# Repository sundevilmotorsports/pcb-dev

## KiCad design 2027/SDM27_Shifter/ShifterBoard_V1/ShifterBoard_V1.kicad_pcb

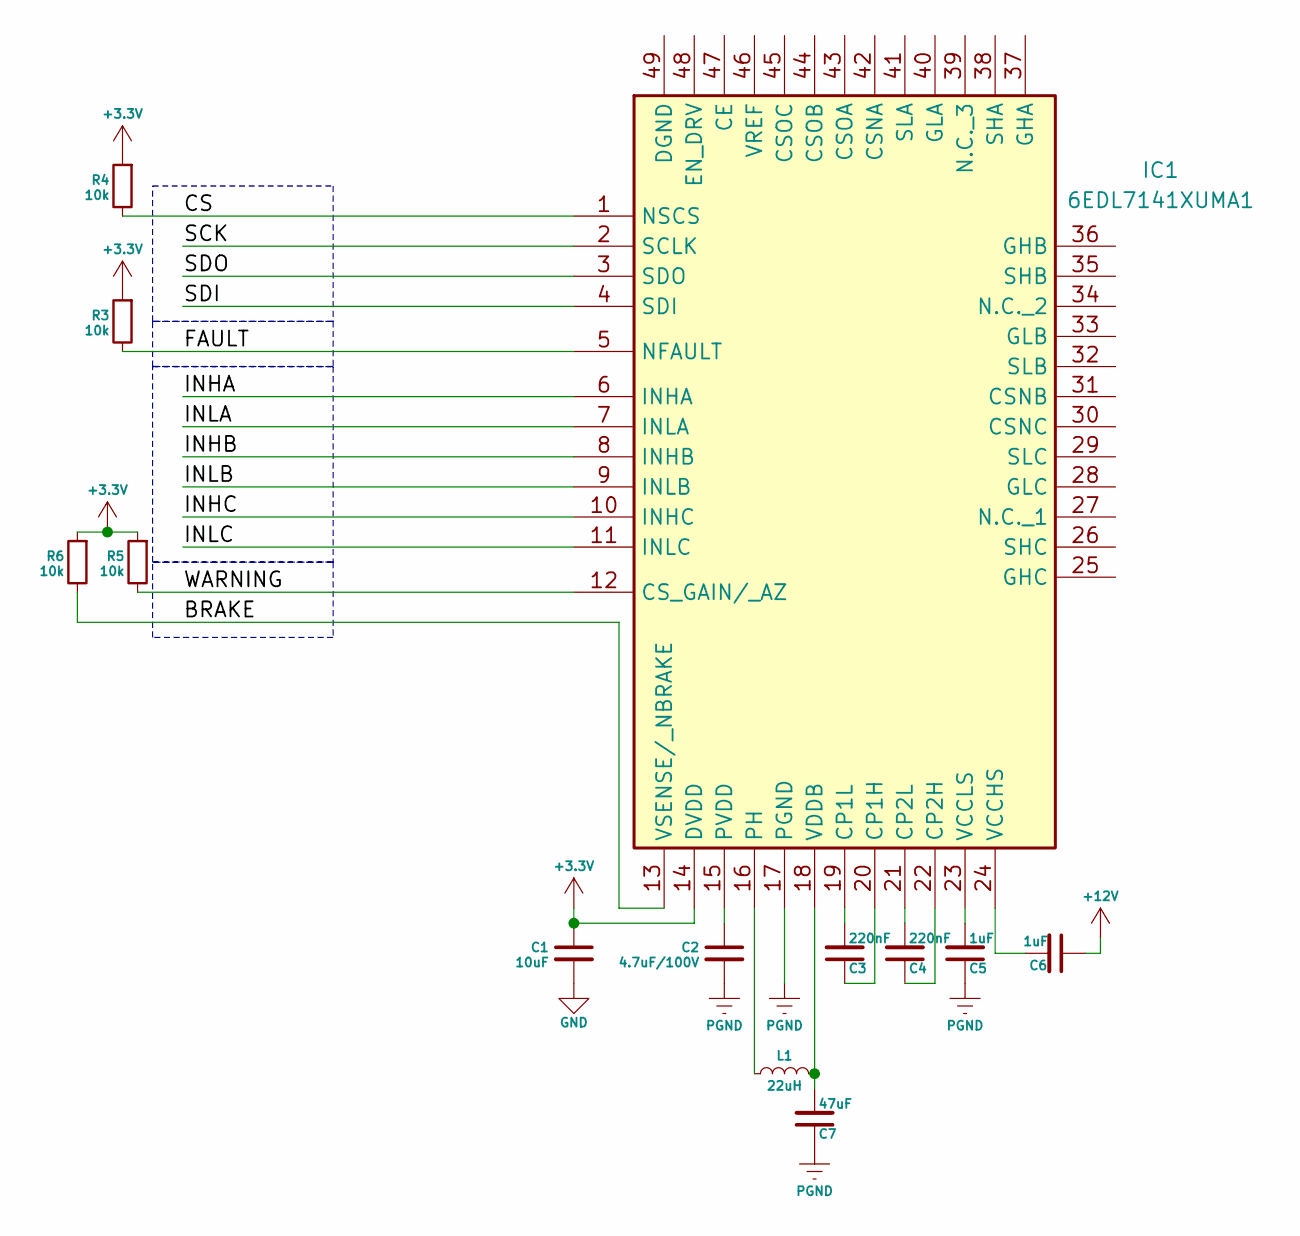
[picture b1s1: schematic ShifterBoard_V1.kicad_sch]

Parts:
C1: 10uF; C_0603_1608Metric
C2: 4.7uF/100V; C_0603_1608Metric
C3, C4: 220nF; C_0603_1608Metric
C5, C6: 1uF; C_0603_1608Metric
C7: 47uF; C_0603_1608Metric
IC1: 6EDL7141XUMA1; Mouser Part Number 726-6EDL7141XUMA1
L1: 22uH; L_1008_2520Metric
R3, R4, R5, R6: 10k; R_0603_1608Metric

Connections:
+3.3V: C1.1, IC1.14 (DVDD), R3.1, R4.1, R5.1, R6.1
+12V: C6.1
/BRAKE: IC1.13 (VSENSE/_NBRAKE), R6.2
/CS: IC1.1 (NSCS), R4.2
/FAULT: IC1.5 (NFAULT), R3.2
/INHA: IC1.6 (INHA)
/INHB: IC1.8 (INHB)
/INHC: IC1.10 (INHC)
/INLA: IC1.7 (INLA)
/INLB: IC1.9 (INLB)
/INLC: IC1.11 (INLC)
/SCK: IC1.2 (SCLK)
/SDI: IC1.4 (SDI)
/SDO: IC1.3 (SDO)
/WARNING: IC1.12 (CS_GAIN/_AZ), R5.2
GND: C1.2
unnamed: C3.1, IC1.20 (CP1H)
unnamed: C3.2, IC1.19 (CP1L)
unnamed: C4.1, IC1.22 (CP2H)
unnamed: C4.2, IC1.21 (CP2L)
unnamed: IC1.16 (PH), L1.1
unnamed: C2.1, IC1.15 (PVDD)
unnamed: C6.2, IC1.24 (VCCHS)
unnamed: C5.2, IC1.23 (VCCLS)
unnamed: C7.2, IC1.18 (VDDB), L1.2
PGND: C2.2, C5.1, C7.1, IC1.17 (PGND)

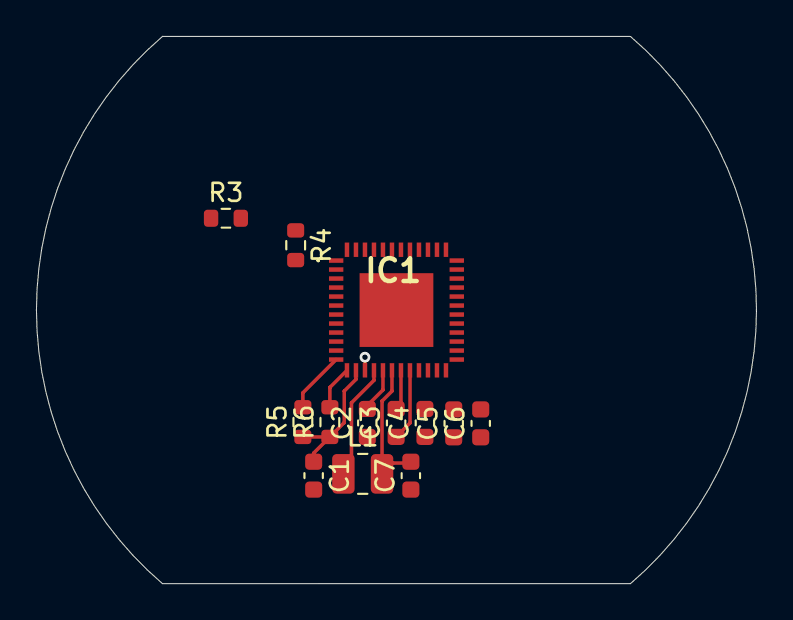
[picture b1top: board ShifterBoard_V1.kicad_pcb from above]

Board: 2 copper layers, 40.0 x 30.4 mm, 13 parts (0 on the bottom side), 15 nets.

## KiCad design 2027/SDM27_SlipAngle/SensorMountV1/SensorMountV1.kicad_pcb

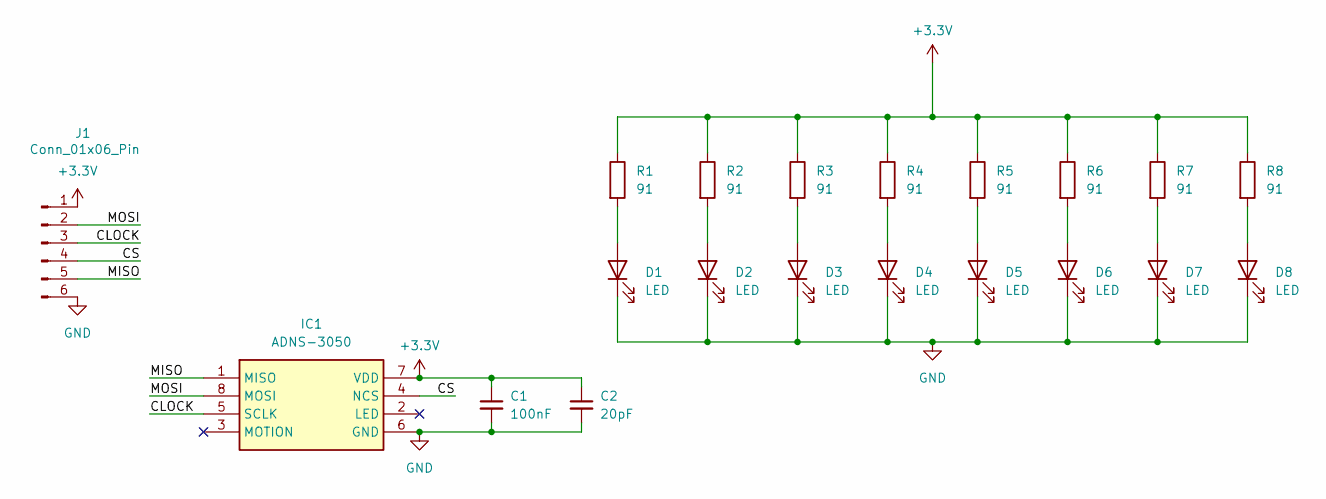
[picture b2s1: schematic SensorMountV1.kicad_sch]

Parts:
C1: 100nF; C_0603_1608Metric
C2: 20pF; C_0603_1608Metric
D1, D2, D3, D4, D5, D6, D7, D8: LED; LED_D5.0mm_Clear
IC1: ADNS-3050; ADNS3050; Mouser Part Number 630-ADNS-3050
J1: Conn_01x06_Pin; JST_XH_B6B-XH-A_1x06_P2.50mm_Vertical
R1, R2, R3, R4, R5, R6, R7, R8: 91; R_Axial_DIN0204_L3.6mm_D1.6mm_P5.08mm_Horizontal

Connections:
+3.3V: C1.1, C2.1, IC1.7 (VDD), J1.1, R1.1, R2.1, R3.1, R4.1, R5.1, R6.1, R7.1, R8.1
/CLOCK: IC1.5 (SCLK), J1.3
/CS: IC1.4 (NCS), J1.4
/MISO: IC1.1 (MISO), J1.5
/MOSI: IC1.8 (MOSI), J1.2
GND: C1.2, C2.2, D1.1 (K), D2.1 (K), D3.1 (K), D4.1 (K), D5.1 (K), D6.1 (K), D7.1 (K), D8.1 (K), IC1.6 (GND), J1.6
unnamed: D1.2 (A), R1.2
unnamed: D2.2 (A), R2.2
unnamed: D3.2 (A), R3.2
unnamed: D4.2 (A), R4.2
unnamed: D5.2 (A), R5.2
unnamed: D6.2 (A), R6.2
unnamed: D7.2 (A), R7.2
unnamed: D8.2 (A), R8.2

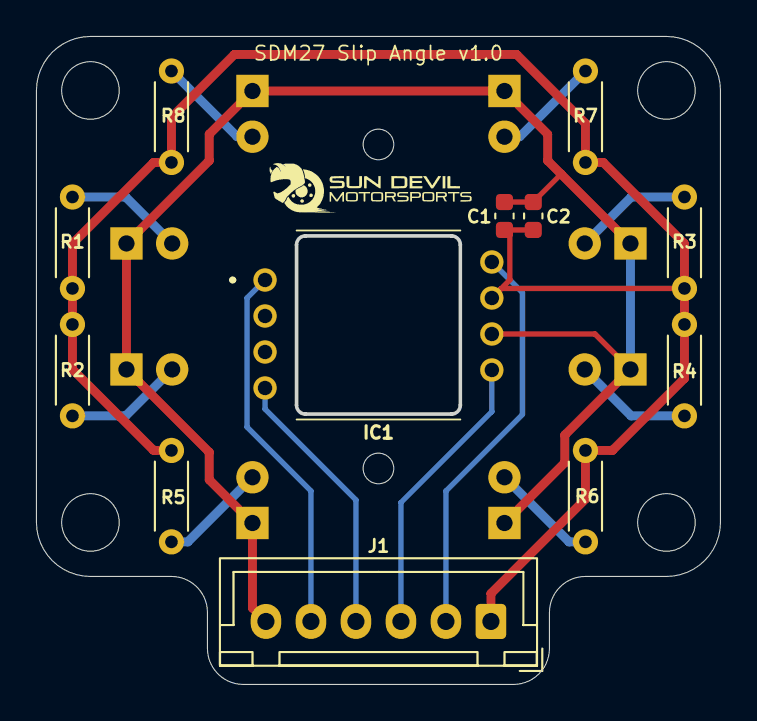
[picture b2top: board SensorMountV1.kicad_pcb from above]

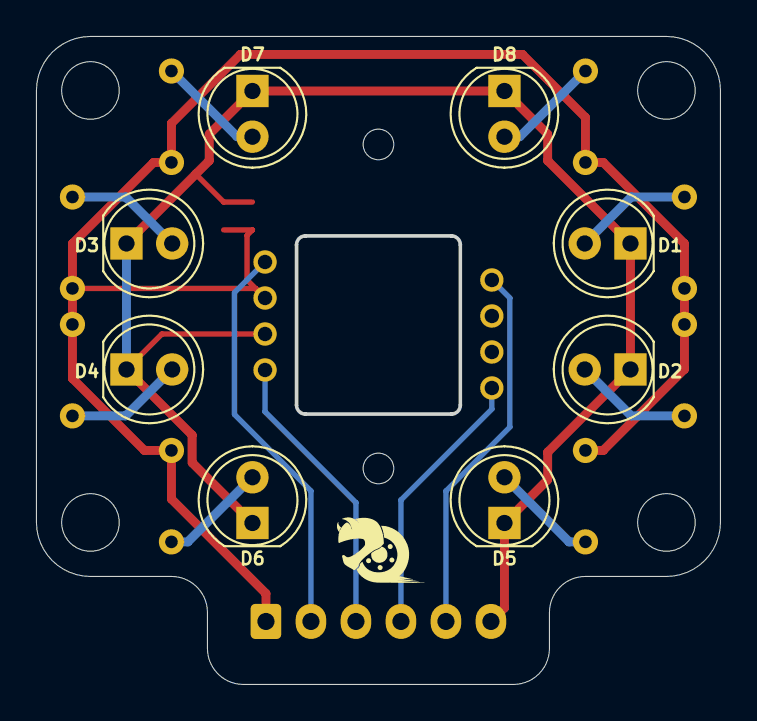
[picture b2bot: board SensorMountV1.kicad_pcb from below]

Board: 2 copper layers, 38.0 x 36.0 mm, 20 parts (8 on the bottom side), 14 nets.

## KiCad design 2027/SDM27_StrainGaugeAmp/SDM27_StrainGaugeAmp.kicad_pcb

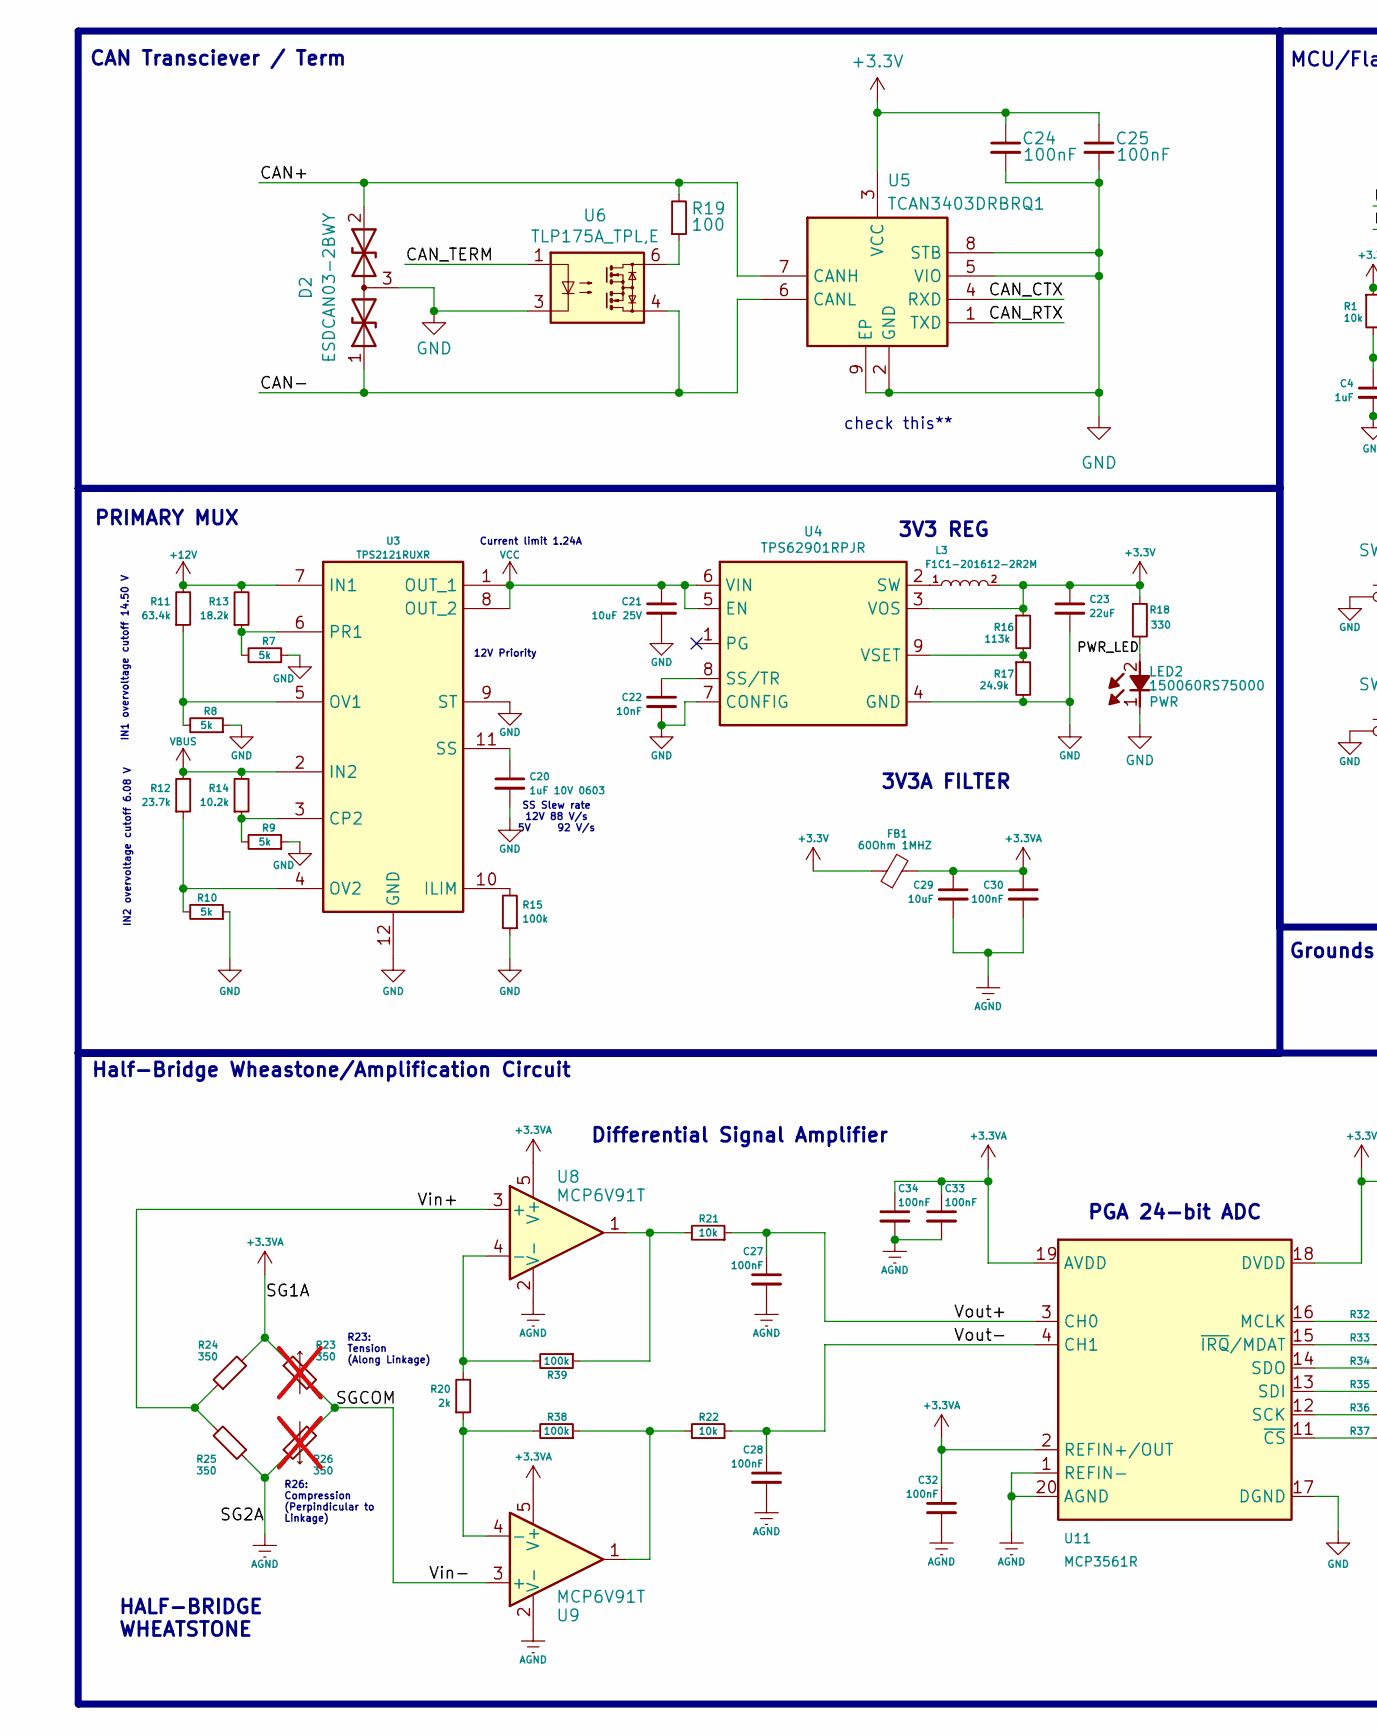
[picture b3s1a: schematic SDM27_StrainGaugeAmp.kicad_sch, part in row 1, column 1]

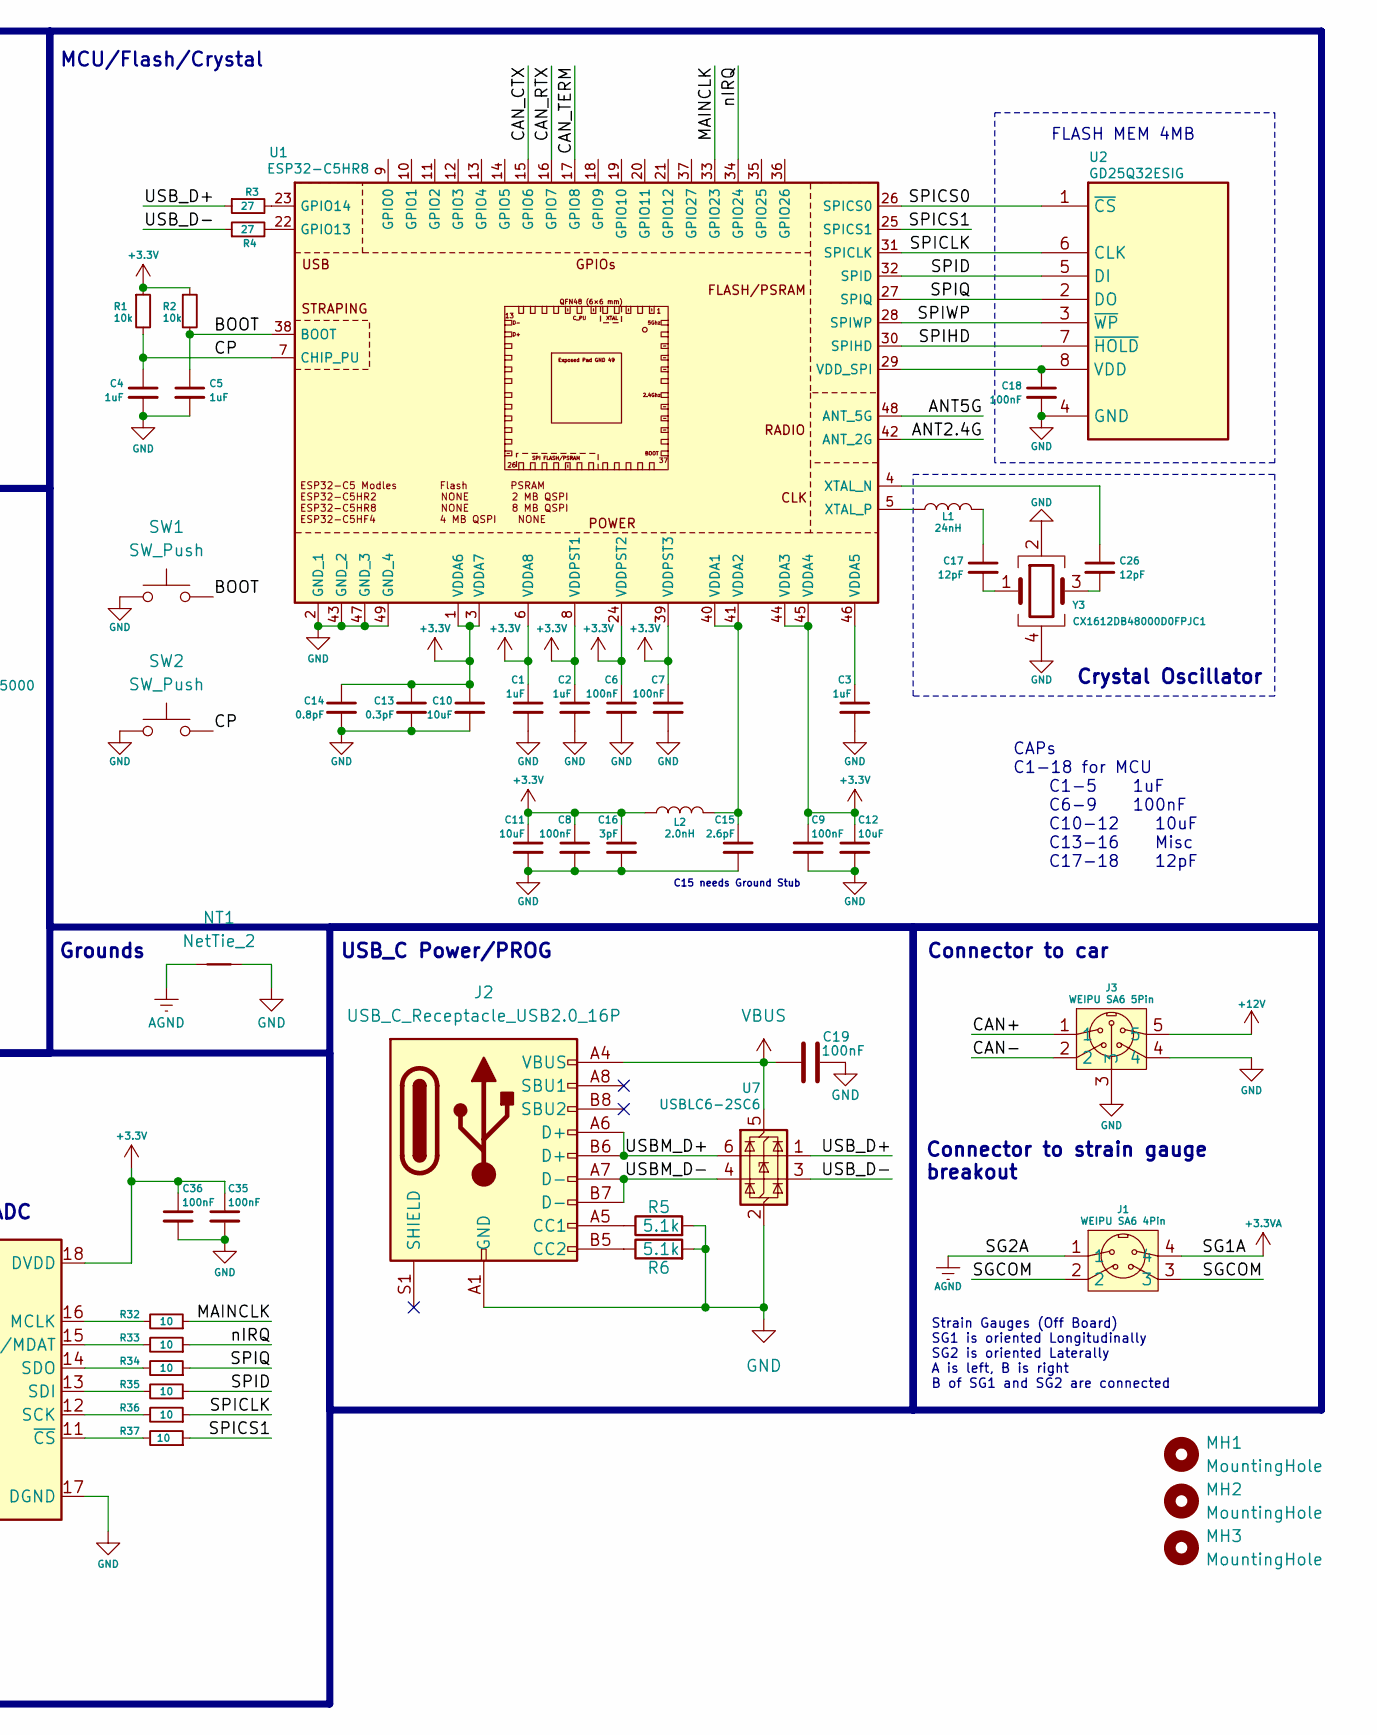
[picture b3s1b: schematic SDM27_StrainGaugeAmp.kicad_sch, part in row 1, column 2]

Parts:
C1, C2, C3, C4, C5: 1uF; C_0603_1608Metric
C6, C7, C8, C9, C18, C19, C24, C25, C27, C28, C30, C32, C33, C34, C35, C36: 100nF; C_0603_1608Metric
C10, C11, C12, C29: 10uF; C_0603_1608Metric
C13: 0.3pF; C_0603_1608Metric
C14: 0.8pF; C_0603_1608Metric
C15: 2.6pF; C_0603_1608Metric
C16: 3pF; C_0603_1608Metric
C17, C26: 12pF; C_0603_1608Metric
C20: 1uF 10V 0603; C_0603_1608Metric
C21: 10uF 25V; C_0603_1608Metric
C22: 10nF; C_0603_1608Metric
C23: 22uF; C_0603_1608Metric
D2: ESDCAN03-2BWY; SOT65P210X110-3N; Mouser Part Number 511-ESDCAN03-2BWY
FB1: 60Ohm 1MHZ; L_0603_1608Metric
J1: WEIPU SA6 4Pin; JST_EH_S4B-EH_1x04_P2.50mm_Horizontal
J2: USB_C_Receptacle_USB2.0_16P; USB_C_Receptacle_G-Switch_GT-USB-7010ASV
J3: WEIPU SA6 5Pin; JST_EH_S5B-EH_1x05_P2.50mm_Horizontal
L1: 24nH; L_0402_1005Metric
L2: 2.0nH; L_0402_1005Metric
L3: F1C1-201612-2R2M; F1C12016122R2M; Mouser Part Number 530-F1C1-201612-2R2M
LED2: 150060RS75000; LEDC1608X80N; Mouser Part Number 710-150060RS75000
MH1, MH2, MH3: MountingHole; MountingHole_2mm
NT1: NetTie_2; NetTie-2_SMD_Pad0.5mm
R1, R2, R21, R22: 10k; R_0603_1608Metric
R3, R4: 27; R_0402_1005Metric
R5, R6: 5.1k; R_0603_1608Metric
R7, R8, R9, R10: 5k; R_0603_1608Metric
R11: 63.4k; R_0603_1608Metric
R12: 23.7k; R_0603_1608Metric
R13: 18.2k; R_0603_1608Metric
R14: 10.2k; R_0603_1608Metric
R15, R38, R39: 100k; R_0603_1608Metric
R16: 113k; R_0603_1608Metric
R17: 24.9k; R_0603_1608Metric
R18: 330; R_0603_1608Metric
R19: 100; R_0603_1608Metric
R20: 2k; R_0603_1608Metric
R23, R26: 350; R_0603_1608Metric; not fitted
R24, R25: 350; R_0603_1608Metric
R32, R33, R34, R35, R36, R37: 10; R_0603_1608Metric
SW1, SW2: SW_Push; SW_SPST_CK_KXT3
U1: ESP32-C5HR8; QFN40P600X600X90-49N-D; Manufacturer_Part_Number ESP32-C5HR8
U2: GD25Q32ESIG; SOP-8-1EP_4.57x4.57mm_P1.27mm_EP4.57x4.45mm; Mouser Part Number 363-GD25Q32ESIG
U3: TPS2121RUXR; Mouser Part Number 595-TPS2121RUXR
U4: TPS62901RPJR; Mouser Part Number 595-TPS62901RPJR
U5: TCAN3403DRBRQ1; SON65P300X300X100-9N-D; Manufacturer_Part_Number TCAN3403DRBRQ1; Mouser Part Number 595-TCAN3403DRBRQ1
U6: TLP175A_TPL,E; TLP266J; Mouser Part Number 757-TLP175A(TPLE
U7: USBLC6-2SC6; SOT-23-6
U8, U9: MCP6V91T; SOT-23-5
U11: MCP3561R; UQFN-20_3x3mm_P0.55mm
Y3: CX1612DB48000D0FPJC1; Mouser Part Number 581-CX1612DB48D0FPJ

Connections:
+3.3V: C1.1, C2.1, C6.1, C7.1, C8.1, C9.1, C10.1, C11.1, C12.1, C13.1, C14.1, C16.1, C23.1, C24.1, C25.1, C35.1, C36.1, FB1.1, L2.2, L3.2, R1.1, R2.1, R16.1, R18.1, U1.1 (VDDA6), U1.3 (VDDA7), U1.6 (VDDA8), U1.8 (VDDPST1), U1.24 (VDDPST2), U1.39 (VDDPST3), U1.44 (VDDA3), U1.45 (VDDA4), U4.3 (VOS), U5.3 (VCC), U11.18 (DVDD)
+3.3VA: C29.1, C30.1, C32.1, C33.1, C34.1, FB1.2, J1.4, R23.1, R24.2, U8.5 (V+), U9.5 (V+), U11.2 (REFIN+/OUT), U11.19 (AVDD)
+12V: J3.5, R11.2, R13.2, U3.7 (IN1)
/ANT2.4G: U1.42 (ANT_2G)
/ANT5G: U1.48 (ANT_5G)
/BOOT: C5.1, R2.2, SW1.2, U1.38 (BOOT)
/CAN+: D2.2, J3.1, R19.2, U5.7 (CANH)
/CAN-: D2.1, J3.2, U5.6 (CANL), U6.4
/CAN_CTX: U1.15 (GPIO6), U5.4 (RXD)
/CAN_RTX: U1.16 (GPIO7), U5.1 (TXD)
/CAN_TERM: U1.17 (GPIO8), U6.1
/CP: C4.1, R1.2, SW2.2, U1.7 (CHIP_PU)
/MAINCLK: R32.1, U1.33 (GPIO23)
/PWR_LED: LED2.2 (A), R18.2
/SGCOM: J1.2, J1.3, R23.2, R26.2, U9.3 (+)
/SPICLK: R36.1, U1.31 (SPICLK), U2.6 (CLK)
/SPICS0: U1.26 (SPICS0), U2.1 (~CS)
/SPICS1: R37.1, U1.25 (SPICS1)
/SPID: R35.1, U1.32 (SPID), U2.5 (DI)
/SPIHD: U1.30 (SPIHD), U2.7 (~HOLD)
/SPIQ: R34.1, U1.27 (SPIQ), U2.2 (DO)
/SPIWP: U1.28 (SPIWP), U2.3 (~WP)
/USBM_D+: J2.A6 (D+), J2.B6 (D+), U7.6 (I/O1)
/USBM_D-: J2.A7 (D-), J2.B7 (D-), U7.4 (I/O2)
/USB_D+: R3.1, U7.1 (I/O1)
/USB_D-: R4.1, U7.3 (I/O2)
/Vin+: R24.1, R25.2, U8.3 (+)
/Vout+: C27.1, R21.1, U11.3 (CH0)
/Vout-: C28.1, R22.1, U11.4 (CH1)
/nIRQ: R33.1, U1.34 (GPIO24)
AGND: C27.2, C28.2, C29.2, C30.2, C32.2, C33.2, C34.2, J1.1, NT1.1, R25.1, R26.1, U8.2 (V-), U9.2 (V-), U11.1 (REFIN-), U11.20 (AGND)
GND: C1.2, C2.2, C3.2, C4.2, C5.2, C6.2, C7.2, C8.2, C9.2, C10.2, C11.2, C12.2, C13.2, C14.2, C15.2, C16.2, C18.2, C19.1, C20.2, C21.2, C22.2, C23.2, C24.2, C25.2, C35.2, C36.2, D2.3, J2.A1 (GND), J2.A12 (GND), J2.B1 (GND), J2.B12 (GND), J3.3, J3.4, LED2.1 (K), NT1.2, R5.2, R6.2, R7.1, R8.1, R9.1, R10.1, R15.1, R17.2, SW1.1, SW2.1, U1.2 (GND_1), U1.43 (GND_2), U1.47 (GND_3), U1.49 (GND_4), U2.4 (GND), U3.9 (ST), U3.12 (GND), U4.4 (GND), U4.7 (CONFIG), U5.2 (GND), U5.5 (VIO), U5.8 (STB), U5.9 (EP), U6.3, U7.2 (GND), U11.17 (DGND), Y3.2, Y3.4
unnamed: C17.1, L1.2
unnamed: C17.2, Y3.1
unnamed: C26.2, Y3.3
unnamed: J2.A5 (CC1), R5.1
unnamed: J2.B5 (CC2), R6.1
unnamed: R19.1, U6.6
unnamed: R21.2, R39.1, U8.1
unnamed: R22.2, R38.1, U9.1
unnamed: R4.2, U1.22 (GPIO13)
unnamed: R3.2, U1.23 (GPIO14)
unnamed: C15.1, L2.1, U1.40 (VDDA1), U1.41 (VDDA2)
unnamed: C3.1, U1.46 (VDDA5)
unnamed: C18.1, U1.29 (VDD_SPI), U2.8 (VDD)
unnamed: C26.1, U1.4 (XTAL_N)
unnamed: L1.1, U1.5 (XTAL_P)
unnamed: R9.2, R14.1, U3.3 (CP2)
unnamed: R15.2, U3.10 (ILIM)
unnamed: R8.2, R11.1, U3.5 (OV1)
unnamed: R10.2, R12.1, U3.4 (OV2)
unnamed: R7.2, R13.1, U3.6 (PR1)
unnamed: C20.1, U3.11 (SS)
unnamed: C22.1, U4.8 (SS/TR)
unnamed: L3.1, U4.2 (SW)
unnamed: R16.2, R17.1, U4.9 (VSET)
unnamed: R20.2, R39.2, U8.4 (-)
unnamed: R20.1, R38.2, U9.4 (-)
unnamed: R32.2, U11.16 (MCLK)
unnamed: R36.2, U11.12 (SCK)
unnamed: R35.2, U11.13 (SDI)
unnamed: R34.2, U11.14 (SDO)
unnamed: R37.2, U11.11 (~CS)
unnamed: R33.2, U11.15 (~IRQ/MDAT)
VBUS: C19.2, J2.A4 (VBUS), J2.A9 (VBUS), J2.B4 (VBUS), J2.B9 (VBUS), R12.2, R14.2, U3.2 (IN2), U7.5 (VBUS)
VCC: C21.1, U3.1 (OUT_1), U3.8 (OUT_2), U4.5 (EN), U4.6 (VIN)

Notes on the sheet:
check this**
FLASH MEM 4MB
3V3 REG
R23: Tension (Along Linkage)
SS Slew rate 12V 88 V/s 5V 92 V/s
Current limit 1.24A
Connector to car
Connector to strain gauge breakout
C15 needs Ground Stub
12V Priority
CAN Transciever / Term
IN2 overvoltage cutoff 6.08 V
MCU/Flash/Crystal
Half-Bridge Wheastone/Amplification Circuit
Differential Signal Amplifier
3V3A FILTER
HALF-BRIDGE WHEATSTONE
R26: Compression (Perpindicular to Linkage)
CAPs C1-18 for MCU C1-5 1uF C6-9 100nF C10-12 10uF C13-16 Misc C17-18 12pF
Crystal Oscillator
PGA 24-bit ADC
PRIMARY MUX
Grounds
Strain Gauges (Off Board) SG1 is oriented Longitudinally SG2 is oriented Laterally A is left, B is right B of SG1 and SG2 are connected
USB_C Power/PROG
IN1 overvoltage cutoff 14.50 V

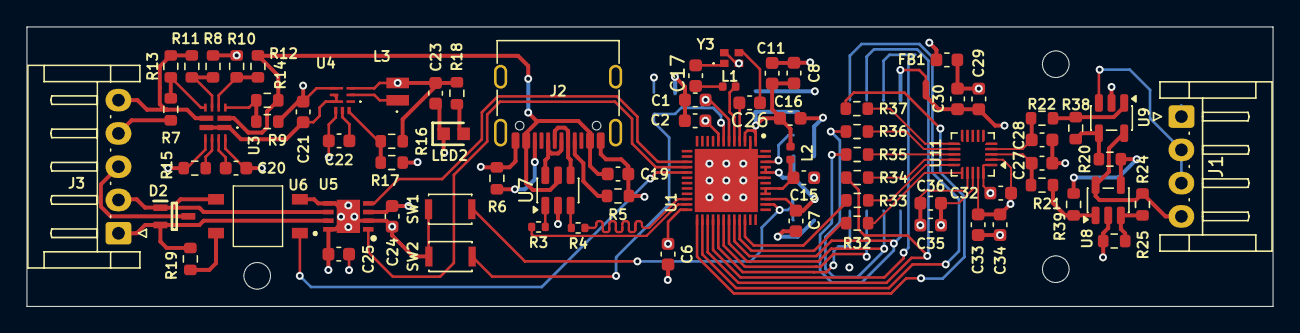
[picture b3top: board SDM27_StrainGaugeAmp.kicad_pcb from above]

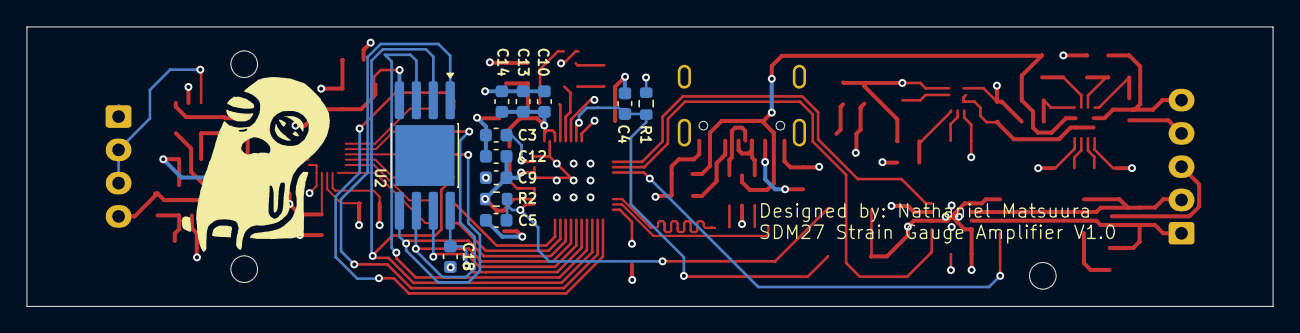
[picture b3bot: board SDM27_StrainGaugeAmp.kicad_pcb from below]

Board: 4 copper layers, 93.6 x 21.0 mm, 91 parts (12 on the bottom side), 64 nets.

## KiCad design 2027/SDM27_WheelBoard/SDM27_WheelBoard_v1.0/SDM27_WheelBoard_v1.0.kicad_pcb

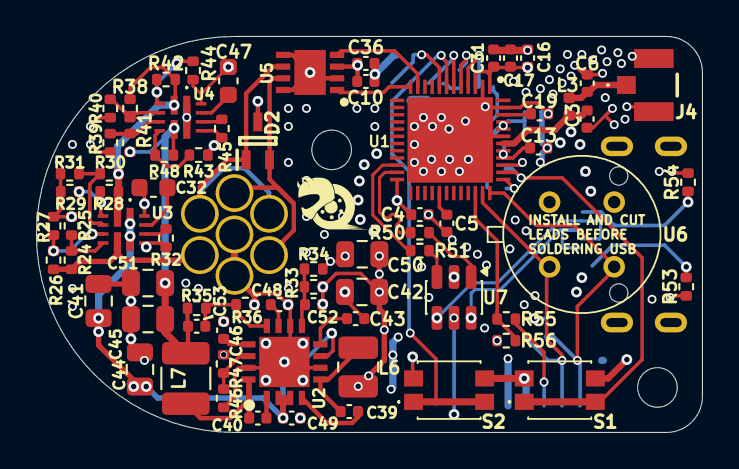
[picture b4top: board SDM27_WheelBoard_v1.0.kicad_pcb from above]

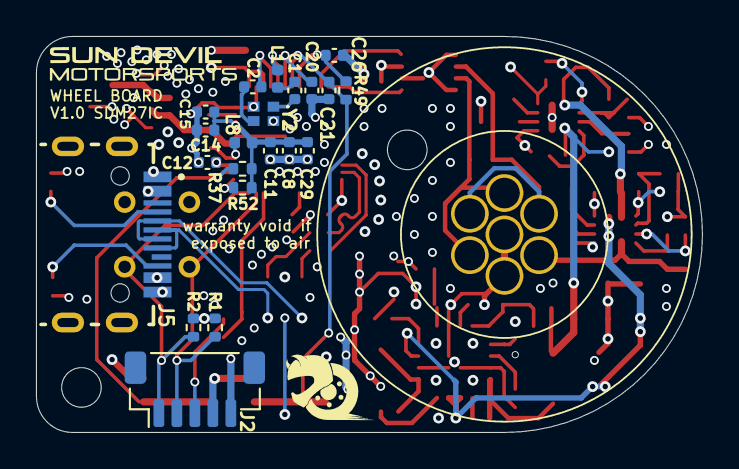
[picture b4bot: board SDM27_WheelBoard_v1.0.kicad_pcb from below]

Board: 4 copper layers, 37.0 x 22.0 mm, 95 parts (22 on the bottom side), 58 nets.

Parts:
C1, C2: 12pF; C_0402_1005Metric
C3, C6: 2.2pF 25V NPO; C_0402_1005Metric
C4, C5, C8, C12, C15: 0.1uF; C_0402_1005Metric
C10, C36, C39, C40, C49: 100nF; C_0402_1005Metric
C11: 3pF; C_0402_1005Metric
C13: 2.6pF; C_0402_1005Metric
C14, C29, C31: 10uF; C_0402_1005Metric
C16: 0.8pF; C_0402_1005Metric
C17: 0.3pF; C_0402_1005Metric
C19, C20, C21, C26, C48: 1uF; C_0402_1005Metric
C32, C47: 1uF 10V 0603; C_0603_1608Metric
C41, C44: 10uF 25V; C_0805_2012Metric
C42, C50: 22uF 10V; C_0805_2012Metric
C43, C46: 10nF; C_0402_1005Metric
C45, C51: 22uF 16V; C_0805_2012Metric
C52, C53: 10pF; C_0402_1005Metric
D2: ESDCAN03-2BWY; SOT65P210X110-3N
H1, H2: M2; MountingHole_2.2mm_M2
J1: WEIPU SA12 7PIN; SA12 7Pin
J2: WEIPU SA6 5Pin; JST_SH_BM05B-SRSS-TB_1x05-1MP_P1.00mm_Vertical
J4: UFL; CONUFL001SMDT
J5: USB4725-03-C-KIT; GCT_USB4730-GF-A_REVA
L1: 24nH; L_0402_1005Metric
L3: 2.8nH; L_0402_1005Metric
L6: 2.2uH; L_1008_2520Metric
L7: 4.7uH; L_1210_3225Metric
L8: 2.0nH; L_0402_1005Metric
R1, R2, R37, R47, R49, R52, R55: 10k; R_0402_1005Metric
R24: 18.2k; R_0402_1005Metric
R25, R27, R29, R31, R39, R40, R43, R44: 5k; R_0402_1005Metric
R26: 63.4k; R_0402_1005Metric
R28, R42: 10.2k; R_0402_1005Metric
R30, R38, R41: 23.7k; R_0402_1005Metric
R32, R35, R45, R46: 100k; R_0402_1005Metric
R33: 73.2k; R_0402_1005Metric
R34: 22.1k; R_0402_1005Metric
R36: 18.0k; R_0402_1005Metric
R48: 4.7k; R_0402_1005Metric
R50, R51: 27; R_0402_1005Metric
R53, R54: 5.1k; R_0402_1005Metric
R56: 20k; R_0402_1005Metric
S1, S2: SKTHBAE010
U1: ESP32-C5HF4; QFN40P600X600X90-49N-D
U2: TPS542951RSAR; QFN65P400X400X100-17N-D
U3, U4: TPS2121RUXR
U5: TCAN3403DRBRQ1; SON65P300X300X100-9N-D
U6: MLX90614ESF-BAA-000-SP; MLX90614ESFBAA000SP
U7: USBLC6-2SC6; SOT-23-6
Y2: CX1612DB48000D0FPJC1

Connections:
+3.3V: C4.1, C8.1, C10.1, C11.1, C12.1, C14.1, C15.1, C16.1, C17.1, C20.1, C26.1, C29.1, C31.1, C36.1, C42.1, C50.1, C52.1, L6.2, L8.2, R1.2, R2.2, R33.2, R37.1, R49.1, R52.1, U1.1 (VDDA6), U1.3 (VDDA7), U1.6 (VDDA8), U1.8 (VDDPST1), U1.24 (VDDPST2), U1.39 (VDDPST3), U1.44 (VDDA3), U1.45 (VDDA4), U5.3 (VCC), U6.3 (VDD)
+5V: J2.5, U4.1 (OUT_1), U4.8 (OUT_2)
+5V PreMUX: C45.1, C51.1, C53.1, L7.1, R35.2, R41.2, R48.2, U4.7 (IN1)
+12V: J1.6, R24.2, R26.2, R47.2, U3.7 (IN1)
/2.4ghz: C3.1, L3.2, U1.42 (ANT_2G)
/5V_EN: R46.2, R47.1, U2.14 (EN2)
/CAN+: D2.2, J1.2, J1.4, U5.7 (CANH)
/CAN-: D2.1, J1.1, J1.3, U5.6 (CANL)
/CAN_CTX: U1.11 (GPIO2), U5.4 (RXD)
/CAN_RTX: U1.12 (GPIO3), U5.1 (TXD)
/SCL: J2.2, R1.1, U1.35 (GPIO25), U6.1 (SCL/VZ)
/SDA: J2.1, R2.1, U1.36 (GPIO26), U6.2 (PWM/SDA)
/USB_D+: J5.A6 (D+), J5.B6 (D+), U7.6 (I/O1)
/USB_D-: J5.A7 (D-), J5.B7 (D-), U7.4 (I/O2)
/WSP_PWM: R55.1, R56.2, U1.34 (GPIO24)
/WSP_RAW: J2.3, R55.2
GND: C3.2, C4.2, C5.2, C6.2, C8.2, C10.2, C11.2, C12.2, C13.2, C14.2, C15.2, C16.2, C17.2, C19.2, C20.2, C21.2, C26.2, C29.2, C31.2, C32.2, C36.2, C41.2, C42.2, C43.1, C44.2, C45.2, C46.2, C47.2, C48.2, C49.2, C50.2, C51.2, D2.3, J1.5, J1.7, J2.4, J4.2 (Shield), J4.3 (Shield), J5.A1 (GND), R25.1, R27.1, R29.1, R31.1, R32.1, R34.1, R36.1, R39.1, R40.1, R43.1, R44.1, R45.1, R46.1, R53.2, R54.2, R56.1, S1.3, S1.4, S2.3, S2.4, U1.2 (GND_1), U1.43 (GND_2), U1.47 (GND_3), U1.49 (GND_4), U2.6 (PGND1), U2.10 (GND), U2.15 (PGND2), U2.17 (EP), U3.9 (ST), U3.12 (GND), U4.9 (ST), U4.12 (GND), U5.2 (GND), U5.5 (VIO), U5.8 (STB), U5.9 (EP), U6.4 (VSS), U7.2 (GND), Y2.2, Y2.4
unnamed: C1.1, L1.2
unnamed: C1.2, Y2.1
unnamed: C2.2, Y2.3
unnamed: R28.1, R29.2, U3.3 (CP2)
unnamed: R32.2, U3.10 (ILIM)
unnamed: R26.1, R27.2, U3.5 (OV1)
unnamed: R30.1, R31.2, U3.4 (OV2)
unnamed: R24.1, R25.2, U3.6 (PR1)
unnamed: C32.1, U3.11 (SS)
unnamed: C43.2, U2.8 (SS1)
unnamed: C46.1, U2.13 (SS2)
unnamed: C39.2, L6.1, U2.5 (SW1)
unnamed: C40.2, L7.2, U2.16 (SW2)
unnamed: C39.1, U2.4 (VBST1)
unnamed: C40.1, U2.1 (VBST2)
unnamed: C52.2, R33.1, R34.2, U2.9 (VFB1)
unnamed: C53.2, R35.1, R36.2, U2.12 (VFB2)
unnamed: C48.1, U2.11 (VREG5)
unnamed: R42.1, R44.2, U4.3 (CP2)
unnamed: R45.2, U4.10 (ILIM)
unnamed: R39.2, R41.1, U4.5 (OV1)
unnamed: R38.1, R40.2, U4.4 (OV2)
unnamed: R43.2, R48.1, U4.6 (PR1)
unnamed: C47.1, U4.11 (SS)
unnamed: R37.2, S1.1, S1.2, U1.38 (BOOT)
unnamed: C21.1, R49.2, S2.1, S2.2, U1.7 (CHIP_PU)
unnamed: R51.2, U1.22 (GPIO13)
unnamed: R50.1, U1.23 (GPIO14)
unnamed: R52.2, U1.37 (GPIO27)
unnamed: C13.1, L8.1, U1.40 (VDDA1), U1.41 (VDDA2)
unnamed: C19.1, U1.46 (VDDA5)
unnamed: C5.1, U1.29 (VDD_SPI)
unnamed: C2.1, U1.4 (XTAL_N)
unnamed: L1.1, U1.5 (XTAL_P)
unnamed: C6.1, J4.1 (A), L3.1
unnamed: J5.A5 (CC1), R54.1
unnamed: J5.B5 (CC2), R53.1
unnamed: R50.2, U7.1 (I/O1)
unnamed: R51.1, U7.3 (I/O2)
VBUS: J5.A4 (VBUS), R28.2, R30.2, R38.2, R42.2, U3.2 (IN2), U4.2 (IN2), U7.5 (VBUS)
VCC: C41.1, C44.1, C49.1, U2.2 (VIN2), U2.3 (VIN1), U2.7 (EN1), U3.1 (OUT_1), U3.8 (OUT_2)

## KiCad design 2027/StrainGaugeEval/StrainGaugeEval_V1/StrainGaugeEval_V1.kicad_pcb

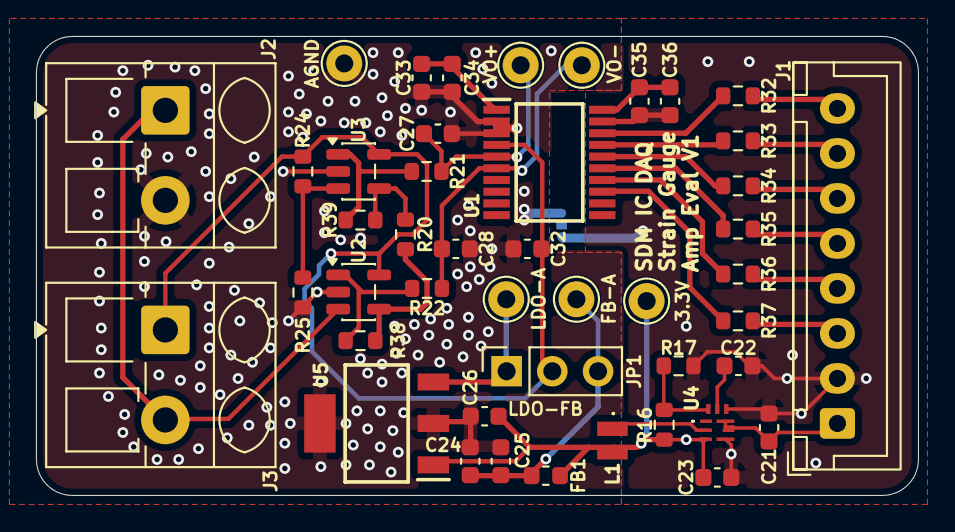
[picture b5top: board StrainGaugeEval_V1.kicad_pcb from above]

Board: 2 copper layers, 49.0 x 25.5 mm, 46 parts (1 on the bottom side), 30 nets.

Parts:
3.3V: REG 3.3V; Pin_D1.0mm_L10.0mm
AGND: AGND; Pin_D1.0mm_L10.0mm
C21: 10uF 25V; C_0603_1608Metric
C22: 10nF; C_0603_1608Metric
C23: 22uF; C_0603_1608Metric
C24: 10uF; C_0603_1608Metric
C25, C27, C28, C32, C33, C34, C35, C36: 100nF; C_0603_1608Metric
C26: 1uF; C_0603_1608Metric
FB1: 60Ohm 1MHZ; L_0603_1608Metric
FB-A: Filter VA; Pin_D1.0mm_L10.0mm
J1: Conn_01x08_Pin; JST_XH_B8B-XH-A_1x08_P2.50mm_Vertical
J2, J3: Screw_Terminal_01x02; TerminalBlock_MetzConnect_Type205_RT04502UBLC_1x02_P5.00mm_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
JP1: A power; PinSocket_1x03_P2.54mm_Vertical
JP2: GND Bridge; SolderJumper-2_P1.3mm_Bridged_Pad1.0x1.5mm
L1: F1C1-201612-2R2M; F1C12016122R2M
LDO-A: LDO VA; Pin_D1.0mm_L10.0mm
R16: 113k; R_0603_1608Metric
R17: 24.9k; R_0603_1608Metric
R20: 2k; R_0603_1608Metric
R21, R22: 10k; R_0603_1608Metric
R24, R25: 350; R_0603_1608Metric
R32, R33, R34, R35, R36, R37: 10; R_0603_1608Metric
R38, R39: 100k; R_0603_1608Metric
U1: MCP3561R-E_ST; SOP65P640X120-20N
U2, U3: MCP6V91T; SOT-23-5
U4: TPS62901RPJR
U5: TC1108-3.0VDBTR; SOT230P700X180-4N
VO+: VO+; Pin_D1.0mm_L10.0mm
VO-: VO-; Pin_D1.0mm_L10.0mm

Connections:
+3.3V: 3.3V.1 (1_1), C23.1, C26.1, C35.1, C36.1, FB1.1, L1.2, R16.1, U1.20 (DVDD), U4.3 (VOS), U5.1 (VIN)
+3.3VA: C32.1, C33.1, C34.1, J3.1, JP1.2 (C), R24.2, U1.1 (AVDD), U1.4 (REFIN+/OUT), U2.5 (V+), U3.5 (V+)
/MAINCLK: J1.8, R32.1
/SGCOM: J2.1, J3.2, U2.3 (+)
/SPICLK: J1.4, R36.1
/SPICS1: J1.3, R37.1
/SPID: J1.5, R35.1
/SPIQ: J1.6, R34.1
/Vin+: R24.1, R25.2, U3.3 (+)
/Vout+: C27.1, R21.1, U1.5 (CH0), VO+.1 (1_1)
/Vout-: C28.1, R22.1, U1.6 (CH1), VO-.1 (1_1)
/nIRQ: J1.7, R33.1
AGND: AGND.1 (1_1), C24.2, C25.2, C26.2, C27.2, C28.2, C32.2, C33.2, C34.2, J2.2, JP2.1 (A), R25.1, U1.2 (AGND), U1.3 (REFIN-), U2.2 (V-), U3.2 (V-), U5.2 (GND), U5.4 (GND_2)
GND: C21.2, C22.2, C23.2, C35.2, C36.2, J1.2, JP2.2 (B), R17.2, U1.19 (DGND), U4.4 (GND), U4.7 (CONFIG)
unnamed: R32.2, U1.18 (MCLK)
unnamed: R36.2, U1.14 (SCK)
unnamed: R35.2, U1.15 (SDI)
unnamed: R34.2, U1.16 (SDO)
unnamed: R37.2, U1.13 (~CS)
unnamed: R33.2, U1.17 (~IRQ/MDAT)
unnamed: JP1.1 (A), LDO-A.1 (1_1), U5.3 (VOUT)
unnamed: C24.1, C25.1, FB1.2, FB-A.1 (1_1), JP1.3 (B)
unnamed: R21.2, R39.1, U3.1
unnamed: R22.2, R38.1, U2.1
unnamed: R20.1, R38.2, U2.4 (-)
unnamed: R20.2, R39.2, U3.4 (-)
unnamed: C22.1, U4.8 (SS/TR)
unnamed: L1.1, U4.2 (SW)
unnamed: R16.2, R17.1, U4.9 (VSET)
VIN: C21.1, J1.1, U4.5 (EN), U4.6 (VIN)

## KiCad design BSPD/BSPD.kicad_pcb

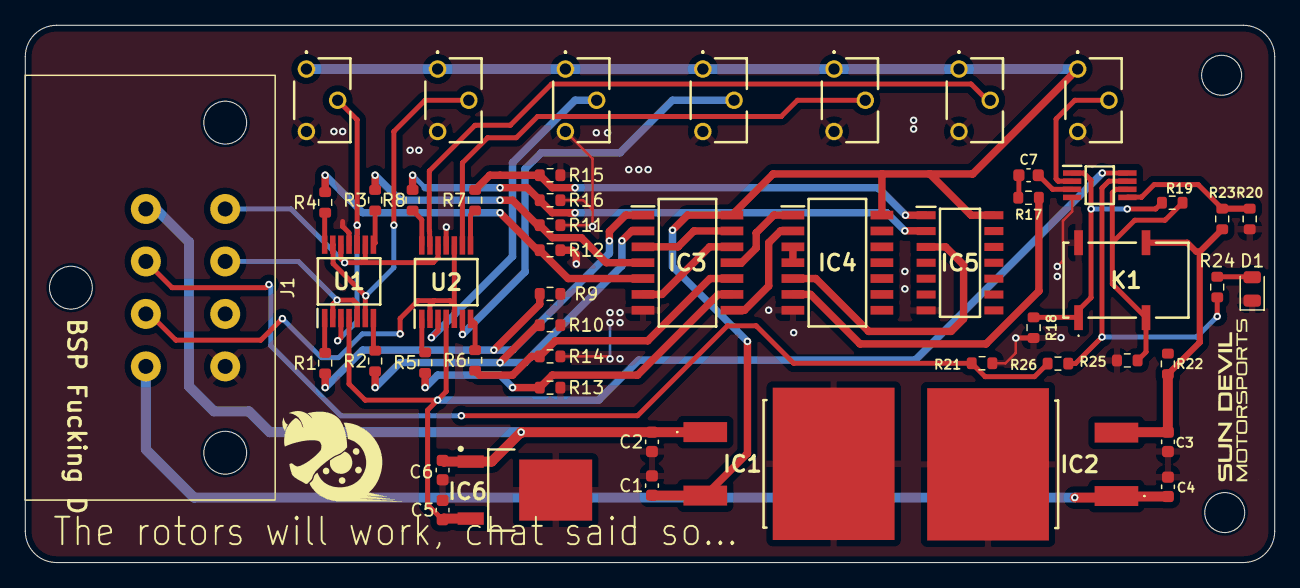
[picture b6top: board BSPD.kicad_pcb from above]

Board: 4 copper layers, 100.0 x 43.0 mm, 54 parts (0 on the bottom side), 47 nets.

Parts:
BR1: LM358AST
C1, C3, C5: 0.1u; C_0603_1608Metric
C2, C4, C6: 0.33u; C_0603_1608Metric
C7: 10uF; C_0603_1608Metric
D1: LED; LED_0805_2012Metric
H1, H2: M3; MountingHole_3.2mm_M3
IC1, IC2: L7805ACD2T-TR; L7805ACD2TTR
IC3, IC4: SN74HC32NSR; SOIC127P780X200-14N
IC5: CD74HC08QM96Q1; SOIC127P600X175-14N
IC6: L78M10ABDT-TR; TO228P972X240-3N
J1: ATM13-08PA-BMXX
K1: IMB03IGR
R1, R2, R3, R4, R5, R6, R7, R8: 22k; R_0603_1608Metric
R9, R10, R11, R12, R13, R14, R15, R16, R23, R25: 30k; R_0603_1608Metric
R17: 10k; R_0603_1608Metric
R18: 15k; R_0603_1608Metric
R19, R22: 220; R_0603_1608Metric
R20: 1k; R_0603_1608Metric
R21: 30K; R_0603_1608Metric
R24: 300; R_0603_1608Metric
R26: 22K; R_0603_1608Metric
U1, U2: LM324
VR**: PV37W502C01B00
VR**#2, VR**#3, VR**#4, VR**#5, VR**#6, VR**#7: PV37W502C01B00

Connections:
+5V: C1.1, IC1.3 (OUTPUT), IC3.14 (VCC), IC4.14 (VCC), IC5.14 (VCC), VR**.1, VR**#2.1, VR**#3.1, VR**#4.1, VR**#5.1, VR**#6.1, VR**#7.1
+10V: BR1.8 (VCC+), C5.1, IC6.3 (OUTPUT), U1.4 (V+), U2.4 (V+)
/BSPD_FAULT: IC4.6 (2Y), R17.1
/B_FAULT: IC3.8 (3Y), IC4.2 (1B)
/B_H: IC3.10 (3B), R6.2, R14.1
/B_HVY: IC5.2 (1B), R8.2, R16.1
/B_L: IC3.9 (3A), R5.2, R13.1
/Brake_High: U2.6 (-), VR**#4.2
/Brake_Low: U2.3 (+), VR**#7.2
/Heavy_Braking: U2.13 (-), VR**.2
/LatchRef: BR1.5 (IN2+), R20.1, R23.1
/RelaySig: BR1.6 (IN2-), K1.3, R19.2, R25.1
/T1_FAULT: IC3.3 (1Y), IC3.13 (4B)
/T1_H: IC3.5 (2B), R4.2, R12.1
/T1_L: IC3.4 (2A), R3.2, R11.1
/T2_FAULT: IC3.6 (2Y), IC3.12 (4A)
/T2_H: IC3.2 (1B), R2.2, R10.1
/T2_L: IC3.1 (1A), R1.2, R9.1
/T+B_FAULT: IC4.3 (1Y), IC4.4 (2A)
/T_10%: IC5.1 (1A), R7.2, R15.1
/T_10%*B_HVY: IC4.5 (2B), IC5.3 (1Y)
/T_FAULT: IC3.11 (4Y), IC4.1 (1A)
/Throttle_10%: U2.9 (-), VR**#2.2
/Throttle_High: U1.6 (-), U1.13 (-), VR**#3.2
/Throttle_Low: U1.3 (+), U1.10 (+), VR**#5.2
BSPD_OUT: J1.6, R21.2, R26.2
BSPD_OUT_PRE: BR1.7 (OUT2), R24.2, R26.1
Brake: J1.7, U2.2 (-), U2.5 (+), U2.10 (+)
GND: BR1.4 (VCC-), C1.2, C2.2, C3.2, C4.2, C5.2, C6.2, D1.1 (K), IC1.2 (GND), IC2.2 (GND), IC3.7 (GND), IC4.7 (GND), IC5.7 (GND), IC6.4 (GND_(TAB)), J1.1, K1.8, R9.2, R10.2, R11.2, R12.2, R13.2, R14.2, R15.2, R16.2, R18.2, R20.2, R21.1, R25.2, U1.11 (V-), U2.11 (V-), VR**.3, VR**#2.3, VR**#3.3, VR**#4.3, VR**#5.3, VR**#6.3, VR**#7.3
IGN_PWR: C2.1, C6.1, IC1.1 (INPUT), IC6.1 (INPUT), J1.5
Latch +5V: C3.1, IC2.3 (OUTPUT), K1.6, R22.1, R23.2
MASTER_PWR: C4.1, IC2.1 (INPUT), J1.8
unnamed: BR1.3 (IN1+), C7.2
unnamed: BR1.2 (IN1-), VR**#6.2
unnamed: BR1.1 (OUT1), K1.1, R18.1, R19.1
unnamed: C7.1, R17.2
unnamed: D1.2 (A), R24.1
unnamed: R1.1, U1.1
unnamed: R2.1, U1.7
unnamed: R3.1, U1.8
unnamed: R4.1, U1.14
unnamed: R5.1, U2.1
unnamed: R6.1, U2.7
unnamed: R7.1, U2.8
unnamed: R8.1, U2.14
Throttle1: J1.4, U1.9 (-), U1.12 (+), U2.12 (+)
Throttle2: J1.3, U1.2 (-), U1.5 (+)
